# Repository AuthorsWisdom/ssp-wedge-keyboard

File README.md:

# Seven Swords Wedge Keyboard

This is an open-hardware 48-key (4 × 12 ortholinear) USB keyboard with an EC11 rotary encoder, built on an RP2040. It's designed for the Seven Swords Wedge desk console by Seven Swords Productions.

| Path | What | Licence |
|---|---|---|
| `keyboard-pcb/` | KiCad 9 project: schematic, PCB, generator scripts, fab outputs, outline DXF | **CERN-OHL-P-2.0** (`keyboard-pcb/LICENSE`) |
| `firmware/` | RMK-based Rust firmware (`rmk-wedge/`) and prebuilt UF2 | **MIT** (`firmware/rmk-wedge/LICENSE`) |

See `keyboard-pcb/README.md` for the build and fab instructions, and `keyboard-pcb/NOTICE.md` for attributions. The RP2040 core follows the Raspberry Pi "Minimal RP2040" reference design (MIT). Raspberry Pi is a trademark of Raspberry Pi Ltd. This is not a Raspberry Pi product.

USB IDs: the firmware currently uses RMK's test VID/PID. A pid.codes ID (1209:5357) is planned and not yet assigned.

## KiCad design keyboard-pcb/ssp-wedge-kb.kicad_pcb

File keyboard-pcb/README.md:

# Seven Swords Wedge — keyboard PCB (KB-P1)

An original 2-layer, 240 × 102 mm, 1.6 mm board: RP2040 + W25Q128 flash, USB-C (USB 2.0 device, 5.1 kΩ CC pull-downs, USBLC6-2 ESD), AMS1117-3.3, 48 MX hot-swap keys (4 × 12, COL2ROW, 1N4148W per key), and an EC11E15244G1 encoder with push. The RP2040 core follows the Raspberry Pi "Minimal RP2040" reference design (MIT, see NOTICE.md). Nothing here comes from Micro Journal.

**Status: design only.** Nothing has been ordered, fabbed, or uploaded, and nothing is tested on hardware.

## Pin map (matches firmware/rmk-wedge/keyboard.toml)
| Signal | GPIO |
|---|---|
| COL0–COL11 | GPIO0–GPIO11 |
| ROW0–ROW3 | GPIO12–GPIO15 |
| ROW4 (encoder push only, key (4,11) via D49) | GPIO18 |
| ENC_A / ENC_B | GPIO16 / GPIO17 |
| Free | GPIO19–GPIO29 (unconnected pads) |

SW49 is BOOTSEL and SW50 is RUN/reset. In the Wedge case they're reached with a SIM-eject pin through the two Ø3 poke holes in the case plate, over PCB (86, 94) = BOOT and (86, 85) = RESET. To flash: hold BOOT, tap RESET, release BOOT, and the `RPI-RP2` drive mounts over the internal cable. You don't need to open the case.

**J2 (3-pin SWD: SWCLK / SWDIO / GND) is DNP. Do not fit it.** A fitted header collides with the case plate (Wedge case v1.1). It's marked DNP on the board and in the schematic, it's left out of `bom-jlc.csv` and `cpl-jlc.csv`, and it's listed in `fab/dnp.csv` and `fab/hand-solder.csv` as DO NOT FIT. If SWD is ever needed, use pogo pins on the bare pads with the board out of the case.

## Files
| Path | What |
|---|---|
| `ssp-wedge-kb.kicad_sch` / `.kicad_pcb` / `.kicad_pro` / `.kicad_dru` | KiCad 9 project |
| `ssp-wedge-kb.net`, `reports/schematic.pdf` | netlist and schematic PDF |
| `reports/erc.rpt`, `reports/drc.rpt` | ERC: 0. DRC: 0 errors, 0 unconnected (notes below) |
| `route/ssp-wedge-kb.dsn` / `.ses` | Freerouting 2.5.0 input and result |
| `fab/ssp-wedge-kb-gerbers.zip` | Gerbers + Excellon drill (PTH/NPTH) + maps + job file |
| `fab/bom-jlc.csv`, `fab/cpl-jlc.csv` | JLCPCB BOM (LCSC #) and CPL: 82 top-side SMD parts |
| `fab/hand-solder.csv` | 48 bottom hot-swap sockets + the EC11 (not in the JLC BOM/CPL), plus a J2 row marked DNP |
| `fab/dnp.csv` | Do-not-fit parts (J2) and why |
| `renders/ssp-wedge-kb-top.png`, `-bottom.png` | 3D renders |
| `mech/ssp-wedge-kb-outline.dxf`, `mech/dims-note.md` | outline, holes, key grid, and keep-outs for the case |
| `LICENSE` | CERN-OHL-P v2 full text (the licence for this hardware) |
| `NOTICE.md` | licence summary and attributions |

## Licence
SPDX-License-Identifier: **CERN-OHL-P-2.0**. Copyright (c) 2026 Seven Swords Productions.

This hardware design is released under the CERN Open Hardware Licence Version 2, Permissive (full text in `LICENSE`). It covers the KiCad sources, the `gen/` scripts, the routing, and the fab outputs in this folder. The licence ID is also on the board's front silkscreen and on the schematic and PCB title blocks. The RP2040 core circuit credits Raspberry Pi's MIT-licensed Minimal RP2040 reference design (see `NOTICE.md`). The firmware (`../firmware`) is MIT, and so is the bot app.

You may use, modify, make and sell this design. Keep the licence notice and the NOTICE attributions. The design comes with no warranty (see CERN-OHL-P §6).

## Regenerate
The whole board is generated by scripts. Don't hand-edit the board, because the next run overwrites it.
```
cd gen
python3 gen_sch.py          # schematic from design.py (+ ERC / netlist)
python3 check_netlist.py    # schematic vs design.py: expect "mismatches: 0"
python3 gen_pcb.py          # placement, outline, holes, netclasses
python3 route.py dsn        # export Specctra DSN
python3 route.py route      # run Freerouting (about 10 to 20 min)
python3 route.py ses        # import the SES, clamp sub-0.15 mm stubs to 0.15, refill zones
cd .. && kicad-cli pcb drc --schematic-parity -o reports/drc.rpt ssp-wedge-kb.kicad_pcb
cd gen && python3 fab.py    # gerbers, drill, BOM/CPL, hand-solder list, renders, DXF
```
Requirements: KiCad 9.0.x (kicad-cli + pcbnew Python) and Freerouting 2.5.0. If you only change placement or the schematic, re-run gen_pcb and then `route.py ses` with the existing .ses to get the same routing back.

## Routing and DRC
- Freerouting reached **0 unrouted, 0 violations**: 1,026 track segments and 127 vias. There's a GND pour on both layers.
- Netclasses:
  - Power (VBUS/GND): 0.25 mm track, 0.6 mm via
  - Rail (+3V3/+1V1): 0.2 mm track, 0.6 mm via
  - Default: 0.2 mm track, 0.5/0.3 mm via
  - Clearance is 0.15 mm for all classes. Everything is within JLC's standard 2-layer capability (0.127 mm track and space, 0.3 mm drill).
- DRC with schematic parity: **0 errors, 0 unconnected.** The remaining warnings are expected:
  - 2 × silk_edge_clearance: the USB-C connector's own silk runs past the board edge where the mouth overhangs. JLC clips it.
  - 15 × net_conflict (parity warnings):
    - 2 for the EC11 mounting lugs, which are tied to GND on the PCB and have no schematic pin
    - 13 for no-connect pins (J1 SBU1/SBU2 and the unused RP2040 GPIO19–29), which have no copper
- `ssp-wedge-kb.kicad_dru` accepts one thermal spoke on the GND pads of two 0402 decoupling caps (C4, C6). They're boxed in by QFN fan-out tracks.

## Before any fab order (all open)
- **USB IDs.** The firmware still uses RMK's test VID/PID. We plan to apply for pid.codes **1209:5357**, which isn't assigned yet. Switch `keyboard.toml` only after the PR is merged.
- **Hardware testing.** Do a hardware bring-up first: check 3V3 rail current, BOOTSEL enumeration, and that flash boots.

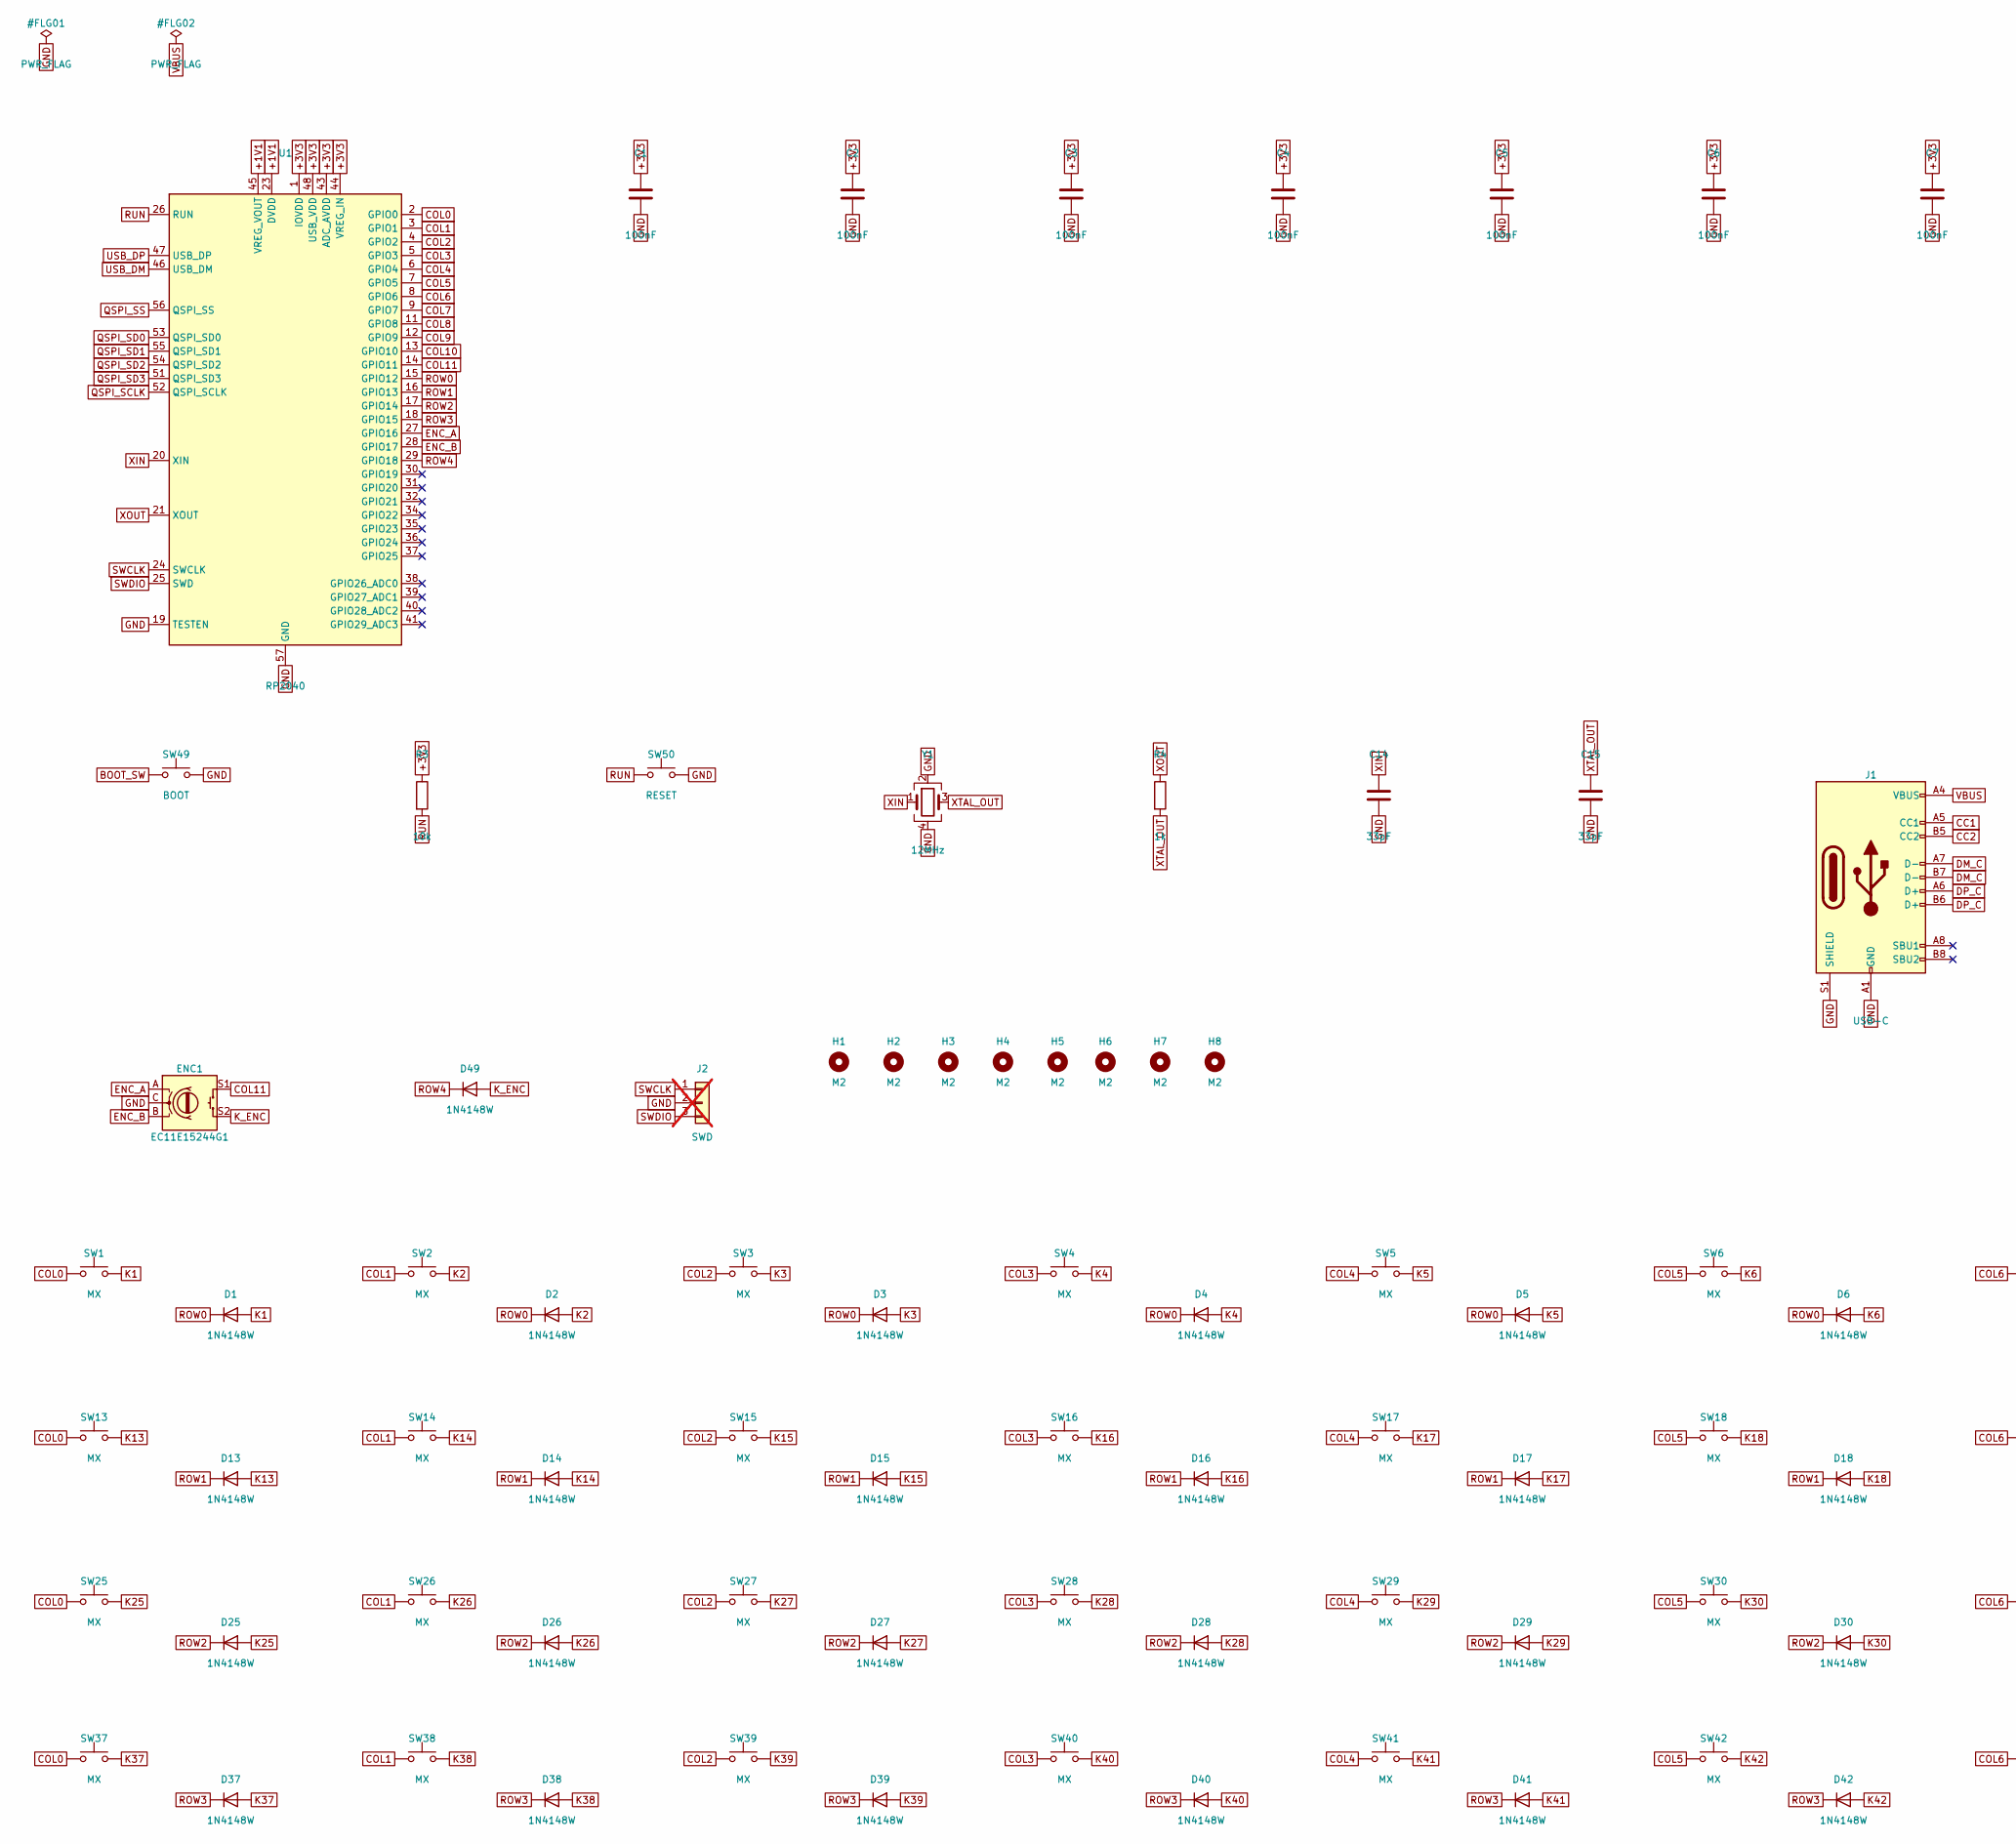
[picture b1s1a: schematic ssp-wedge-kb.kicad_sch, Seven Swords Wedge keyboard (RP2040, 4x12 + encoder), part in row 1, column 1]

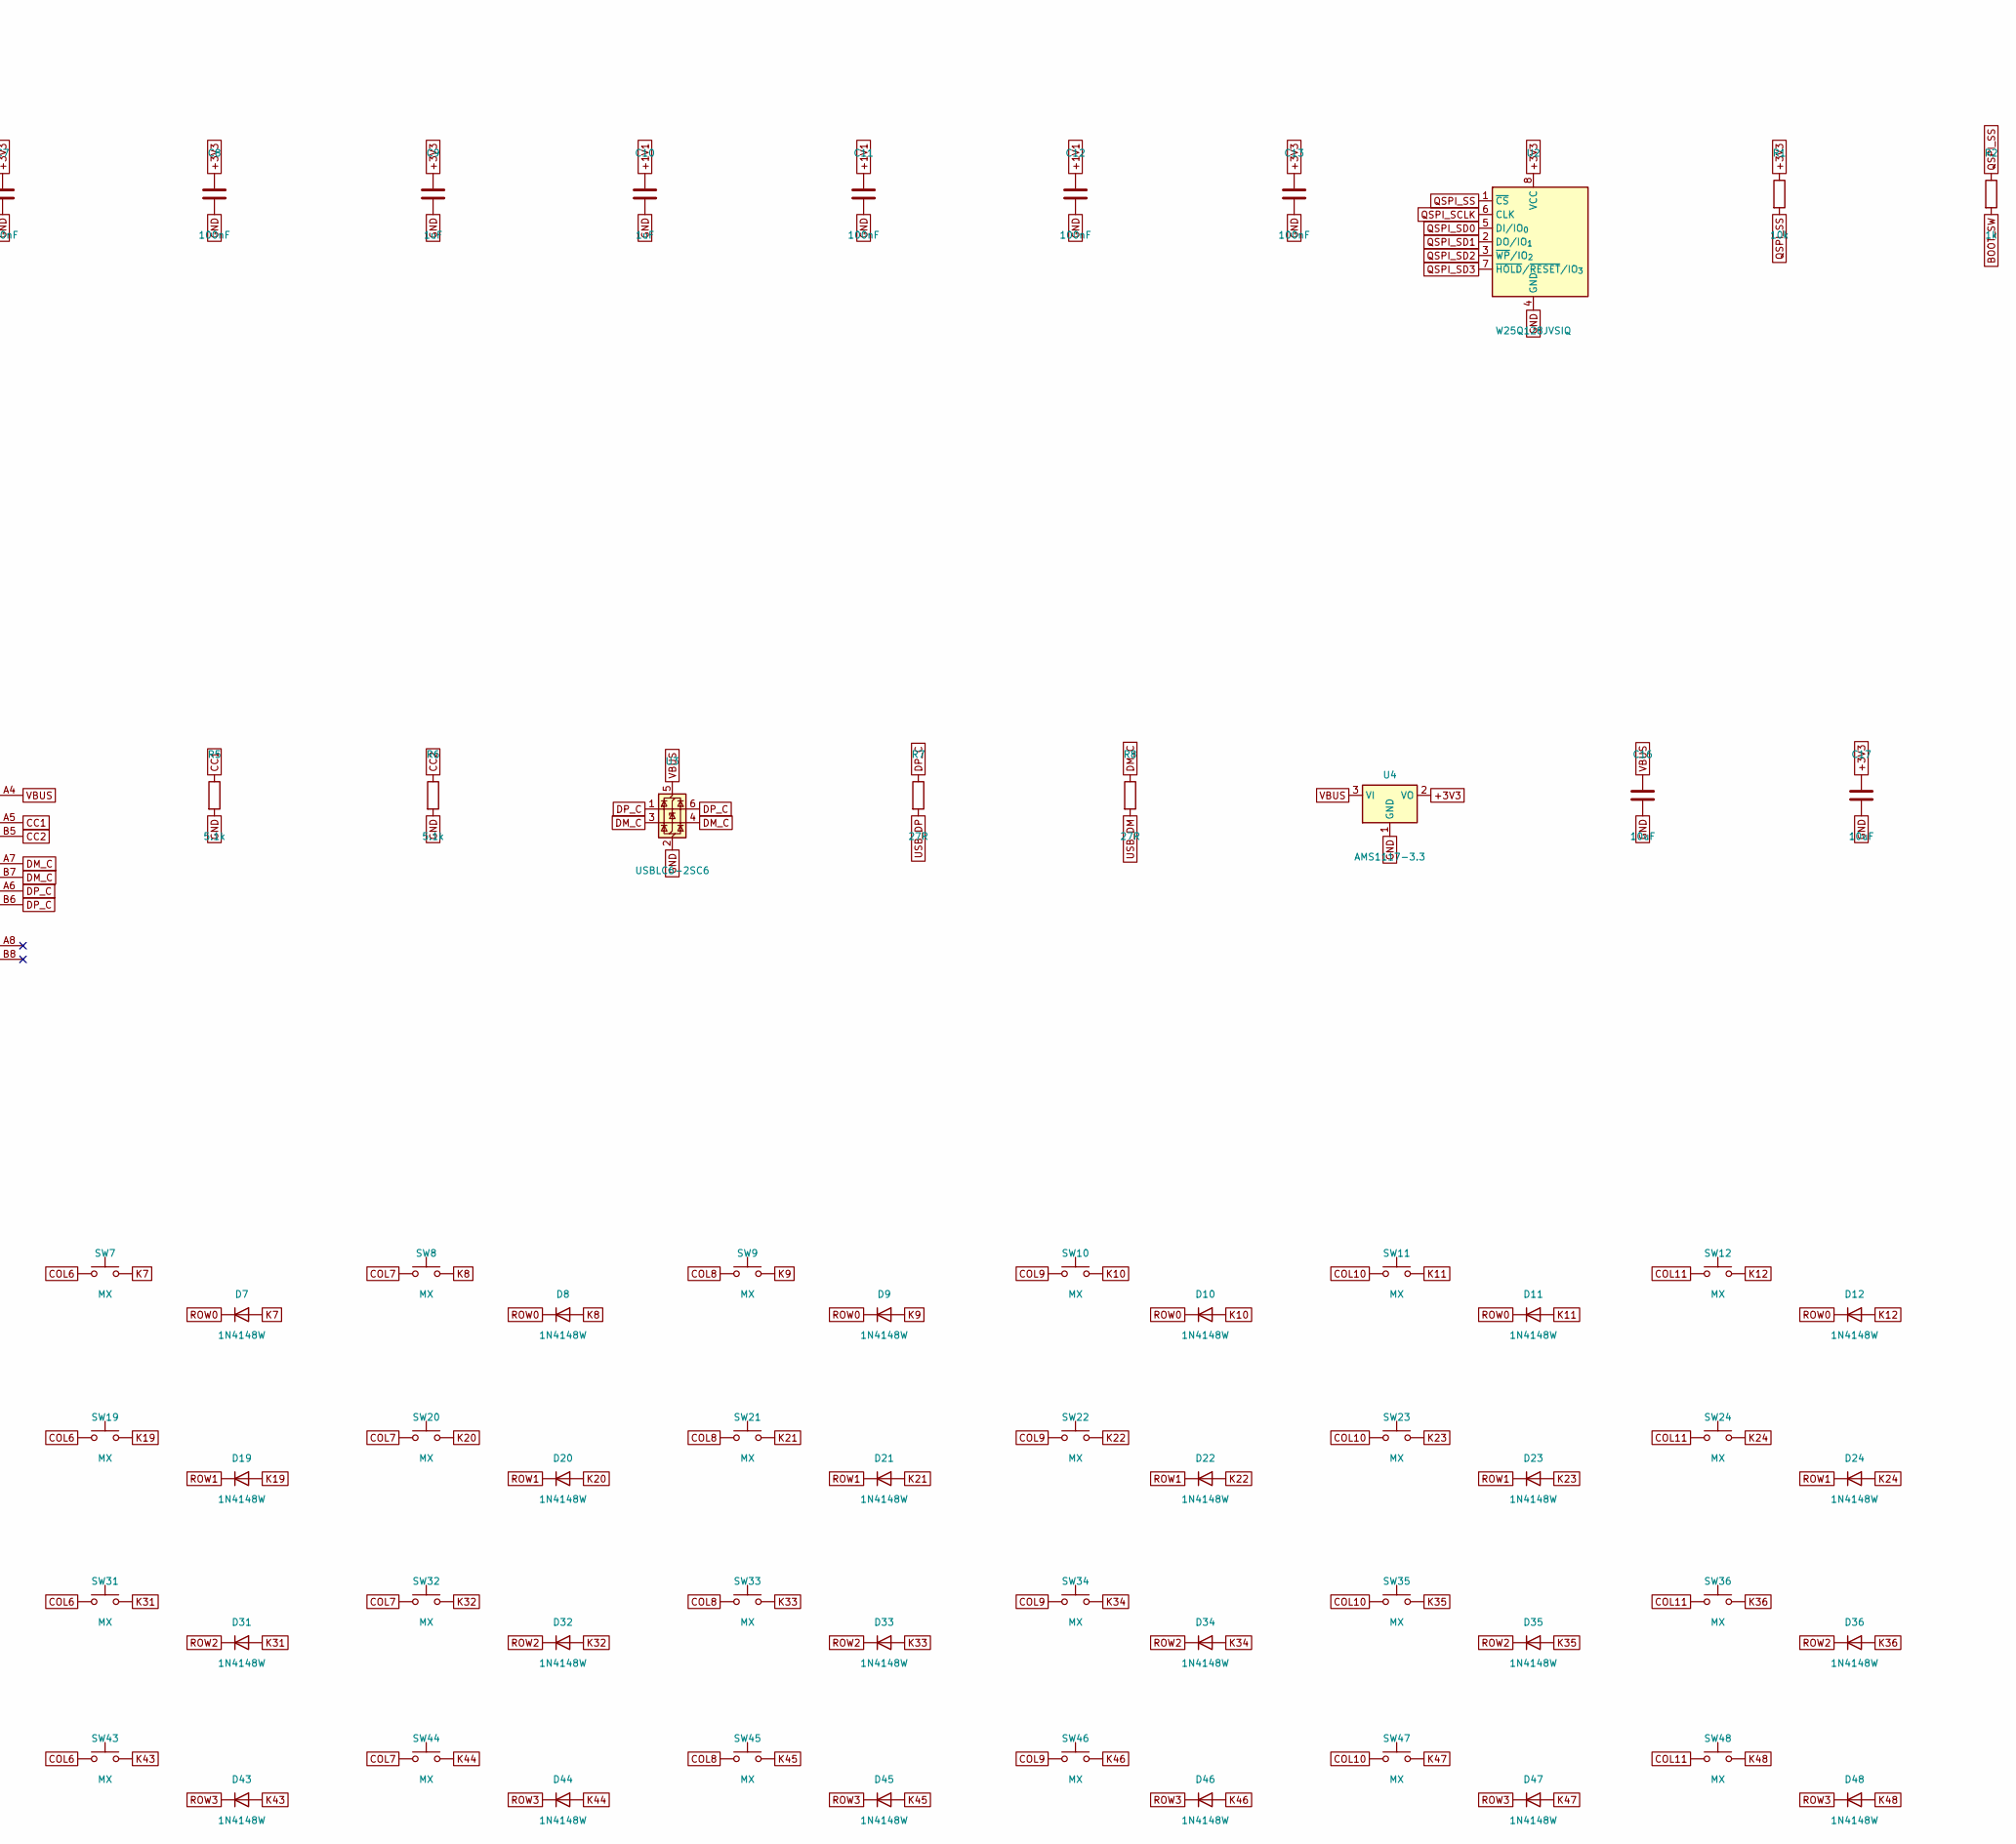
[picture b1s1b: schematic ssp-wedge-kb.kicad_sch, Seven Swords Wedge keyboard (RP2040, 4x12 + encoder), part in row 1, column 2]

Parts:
C1, C2, C3, C4, C5, C6, C7, C8, C11, C12, C13: 100nF; C_0402_1005Metric; LCSC C1525
C9, C10: 1uF; C_0402_1005Metric; LCSC C52923
C14, C15: 33pF; C_0402_1005Metric; LCSC C1562
C16, C17: 10uF; C_0805_2012Metric; LCSC C15850
D1, D2, D3, D4, D5, D6, D7, D8, D9, D10, D11, D12, D13, D14, D15, D16, D17, D18, D19, D20, D21, D22, D23, D24, D25, D26, D27, D28, D29, D30, D31, D32, D33, D34, D35, D36, D37, D38, D39, D40, D41, D42, D43, D44, D45, D46, D47, D48, D49: 1N4148W; D_SOD-123; LCSC C81598
ENC1: EC11E15244G1; RotaryEncoder_Alps_EC11E-Switch_Vertical_H20mm; LCSC C370970
H1, H2, H3, H4, H5, H6, H7, H8: M2; MountingHole_2.2mm_M2
J1: USB-C; USB_C_Receptacle_HRO_TYPE-C-31-M-12; LCSC C165948
J2: SWD; PinHeader_1x03_P2.54mm_Vertical; not fitted
R1, R3: 10k; R_0402_1005Metric; LCSC C25744
R2, R4: 1k; R_0402_1005Metric; LCSC C11702
R5, R6: 5.1k; R_0402_1005Metric; LCSC C25905
R7, R8: 27R; R_0402_1005Metric; LCSC C25100
SW1, SW2, SW3, SW4, SW5, SW6, SW7, SW8, SW9, SW10, SW11, SW12, SW13, SW14, SW15, SW16, SW17, SW18, SW19, SW20, SW21, SW22, SW23, SW24, SW25, SW26, SW27, SW28, SW29, SW30, SW31, SW32, SW33, SW34, SW35, SW36, SW37, SW38, SW39, SW40, SW41, SW42, SW43, SW44, SW45, SW46, SW47, SW48: MX; SW_MX_Hotswap_Kailh_1.00u; LCSC C5156480
SW49: BOOT; SW_Push_1P1T_XKB_TS-1187A; LCSC C318884
SW50: RESET; SW_Push_1P1T_XKB_TS-1187A; LCSC C318884
U1: RP2040; QFN-56-1EP_7x7mm_P0.4mm_EP3.2x3.2mm; LCSC C2040
U2: W25Q128JVSIQ; SOIC-8_5.3x5.3mm_P1.27mm; LCSC C97521
U3: USBLC6-2SC6; SOT-23-6; LCSC C7519
U4: AMS1117-3.3; SOT-223-3_TabPin2; LCSC C6186
Y1: 12MHz; Crystal_SMD_3225-4Pin_3.2x2.5mm; LCSC C9002

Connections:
+1V1: C10.1, C11.1, C12.1, U1.23 (DVDD), U1.45 (VREG_VOUT), U1.50 (DVDD)
+3V3: C1.1, C2.1, C3.1, C4.1, C5.1, C6.1, C7.1, C8.1, C9.1, C13.1, C17.1, R1.1, R3.1, U1.1 (IOVDD), U1.10 (IOVDD), U1.22 (IOVDD), U1.33 (IOVDD), U1.42 (IOVDD), U1.43 (ADC_AVDD), U1.44 (VREG_IN), U1.48 (USB_VDD), U1.49 (IOVDD), U2.8 (VCC), U4.2 (VO)
BOOT_SW: R2.2, SW49.1
CC1: J1.A5 (CC1), R5.1
CC2: J1.B5 (CC2), R6.1
COL0: SW1.1, SW13.1, SW25.1, SW37.1, U1.2 (GPIO0)
COL1: SW2.1, SW14.1, SW26.1, SW38.1, U1.3 (GPIO1)
COL2: SW3.1, SW15.1, SW27.1, SW39.1, U1.4 (GPIO2)
COL3: SW4.1, SW16.1, SW28.1, SW40.1, U1.5 (GPIO3)
COL4: SW5.1, SW17.1, SW29.1, SW41.1, U1.6 (GPIO4)
COL5: SW6.1, SW18.1, SW30.1, SW42.1, U1.7 (GPIO5)
COL6: SW7.1, SW19.1, SW31.1, SW43.1, U1.8 (GPIO6)
COL7: SW8.1, SW20.1, SW32.1, SW44.1, U1.9 (GPIO7)
COL8: SW9.1, SW21.1, SW33.1, SW45.1, U1.11 (GPIO8)
COL9: SW10.1, SW22.1, SW34.1, SW46.1, U1.12 (GPIO9)
COL10: SW11.1, SW23.1, SW35.1, SW47.1, U1.13 (GPIO10)
COL11: ENC1.S1, SW12.1, SW24.1, SW36.1, SW48.1, U1.14 (GPIO11)
DM_C: J1.A7 (D-), J1.B7 (D-), R8.1, U3.3 (I/O2), U3.4 (I/O2)
DP_C: J1.A6 (D+), J1.B6 (D+), R7.1, U3.1 (I/O1), U3.6 (I/O1)
ENC_A: ENC1.A, U1.27 (GPIO16)
ENC_B: ENC1.B, U1.28 (GPIO17)
GND: C1.2, C2.2, C3.2, C4.2, C5.2, C6.2, C7.2, C8.2, C9.2, C10.2, C11.2, C12.2, C13.2, C14.2, C15.2, C16.2, C17.2, ENC1.C, ENC1.MP, J1.A1 (GND), J1.A12 (GND), J1.B1 (GND), J1.B12 (GND), J1.S1 (SHIELD), J2.2, R5.2, R6.2, SW49.2, SW50.2, U1.19 (TESTEN), U1.57 (GND), U2.4 (GND), U3.2 (GND), U4.1 (GND), Y1.2, Y1.4
K1: D1.2 (A), SW1.2
K2: D2.2 (A), SW2.2
K3: D3.2 (A), SW3.2
K4: D4.2 (A), SW4.2
K5: D5.2 (A), SW5.2
K6: D6.2 (A), SW6.2
K7: D7.2 (A), SW7.2
K8: D8.2 (A), SW8.2
K9: D9.2 (A), SW9.2
K10: D10.2 (A), SW10.2
K11: D11.2 (A), SW11.2
K12: D12.2 (A), SW12.2
K13: D13.2 (A), SW13.2
K14: D14.2 (A), SW14.2
K15: D15.2 (A), SW15.2
K16: D16.2 (A), SW16.2
K17: D17.2 (A), SW17.2
K18: D18.2 (A), SW18.2
K19: D19.2 (A), SW19.2
K20: D20.2 (A), SW20.2
K21: D21.2 (A), SW21.2
K22: D22.2 (A), SW22.2
K23: D23.2 (A), SW23.2
K24: D24.2 (A), SW24.2
K25: D25.2 (A), SW25.2
K26: D26.2 (A), SW26.2
K27: D27.2 (A), SW27.2
K28: D28.2 (A), SW28.2
K29: D29.2 (A), SW29.2
K30: D30.2 (A), SW30.2
K31: D31.2 (A), SW31.2
K32: D32.2 (A), SW32.2
K33: D33.2 (A), SW33.2
K34: D34.2 (A), SW34.2
K35: D35.2 (A), SW35.2
K36: D36.2 (A), SW36.2
K37: D37.2 (A), SW37.2
K38: D38.2 (A), SW38.2
K39: D39.2 (A), SW39.2
K40: D40.2 (A), SW40.2
K41: D41.2 (A), SW41.2
K42: D42.2 (A), SW42.2
K43: D43.2 (A), SW43.2
K44: D44.2 (A), SW44.2
K45: D45.2 (A), SW45.2
K46: D46.2 (A), SW46.2
K47: D47.2 (A), SW47.2
K48: D48.2 (A), SW48.2
K_ENC: D49.2 (A), ENC1.S2
QSPI_SCLK: U1.52 (QSPI_SCLK), U2.6 (CLK)
QSPI_SD0: U1.53 (QSPI_SD0), U2.5 (DI/IO_{0})
QSPI_SD1: U1.55 (QSPI_SD1), U2.2 (DO/IO_{1})
QSPI_SD2: U1.54 (QSPI_SD2), U2.3 (~WP/IO_{2})
QSPI_SD3: U1.51 (QSPI_SD3), U2.7 (~HOLD/~RESET/IO_{3})
QSPI_SS: R1.2, R2.1, U1.56 (QSPI_SS), U2.1 (~CS)
ROW0: D1.1 (K), D2.1 (K), D3.1 (K), D4.1 (K), D5.1 (K), D6.1 (K), D7.1 (K), D8.1 (K), D9.1 (K), D10.1 (K), D11.1 (K), D12.1 (K), U1.15 (GPIO12)
ROW1: D13.1 (K), D14.1 (K), D15.1 (K), D16.1 (K), D17.1 (K), D18.1 (K), D19.1 (K), D20.1 (K), D21.1 (K), D22.1 (K), D23.1 (K), D24.1 (K), U1.16 (GPIO13)
ROW2: D25.1 (K), D26.1 (K), D27.1 (K), D28.1 (K), D29.1 (K), D30.1 (K), D31.1 (K), D32.1 (K), D33.1 (K), D34.1 (K), D35.1 (K), D36.1 (K), U1.17 (GPIO14)
ROW3: D37.1 (K), D38.1 (K), D39.1 (K), D40.1 (K), D41.1 (K), D42.1 (K), D43.1 (K), D44.1 (K), D45.1 (K), D46.1 (K), D47.1 (K), D48.1 (K), U1.18 (GPIO15)
ROW4: D49.1 (K), U1.29 (GPIO18)
RUN: R3.2, SW50.1, U1.26 (RUN)
SWCLK: J2.1, U1.24 (SWCLK)
SWDIO: J2.3, U1.25 (SWD)
USB_DM: R8.2, U1.46 (USB_DM)
USB_DP: R7.2, U1.47 (USB_DP)
VBUS: C16.1, J1.A4 (VBUS), J1.A9 (VBUS), J1.B4 (VBUS), J1.B9 (VBUS), U3.5 (VBUS), U4.3 (VI)
XIN: C14.1, U1.20 (XIN), Y1.1
XOUT: R4.1, U1.21 (XOUT)
XTAL_OUT: C15.1, R4.2, Y1.3

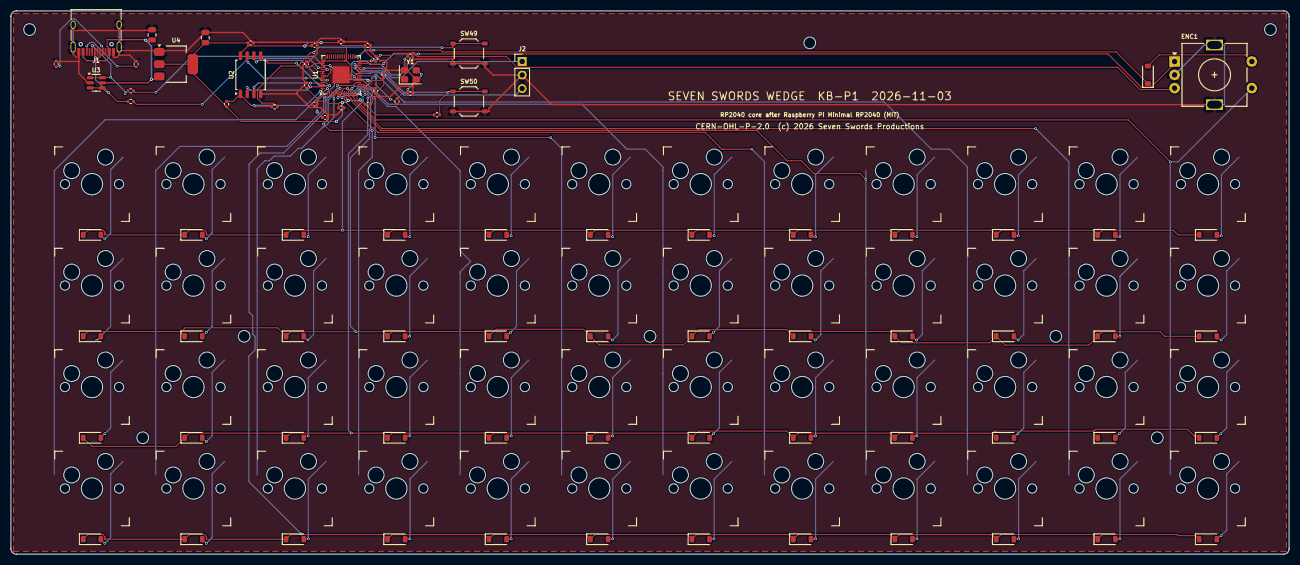
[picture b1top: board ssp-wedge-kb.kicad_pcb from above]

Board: 2 copper layers, 240.0 x 102.0 mm, 140 parts (0 on the bottom side), 91 nets.

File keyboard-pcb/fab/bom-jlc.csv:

Comment,Designator,Footprint,LCSC Part #
100nF,"C1,C2,C3,C4,C5,C6,C7,C8,C11,C12,C13",C_0402_1005Metric,C1525
1uF,"C9,C10",C_0402_1005Metric,C52923
33pF,"C14,C15",C_0402_1005Metric,C1562
10uF,"C16,C17",C_0805_2012Metric,C15850
1N4148W,"D1,D2,D3,D4,D5,D6,D7,D8,D9,D10,D11,D12,D13,D14,D15,D16,D17,D18,D19,D20,D21,D22,D23,D24,D25,D26,D27,D28,D29,D30,D31,D32,D33,D34,D35,D36,D37,D38,D39,D40,D41,D42,D43,D44,D45,D46,D47,D48,D49",D_SOD-123,C81598
USB-C,J1,USB_C_Receptacle_HRO_TYPE-C-31-M-12,C165948
10k,"R1,R3",R_0402_1005Metric,C25744
1k,"R2,R4",R_0402_1005Metric,C11702
5.1k,"R5,R6",R_0402_1005Metric,C25905
27R,"R7,R8",R_0402_1005Metric,C25100
BOOT,SW49,SW_Push_1P1T_XKB_TS-1187A,C318884
RESET,SW50,SW_Push_1P1T_XKB_TS-1187A,C318884
RP2040,U1,QFN-56-1EP_7x7mm_P0.4mm_EP3.2x3.2mm,C2040
W25Q128JVSIQ,U2,SOIC-8_5.3x5.3mm_P1.27mm,C97521
USBLC6-2SC6,U3,SOT-23-6,C7519
AMS1117-3.3,U4,SOT-223-3_TabPin2,C6186
12MHz,Y1,Crystal_SMD_3225-4Pin_3.2x2.5mm,C9002

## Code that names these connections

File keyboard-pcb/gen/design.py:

"""Seven Swords Wedge keyboard PCB: single source of truth for parts and nets.

Original SSP design. The RP2040 support circuit (flash, crystal, decoupling,
USB series resistors, BOOT/RUN) follows Raspberry Pi's MIT-licensed
"Minimal RP2040 board" reference design (Raspberry Pi Ltd).
See ../NOTICE.md.
"""
ROWS, COLS = 4, 12
PITCH = 19.05

# ---- GPIO map (keep in sync with firmware/keyboard.toml) ----
COL_GPIO = list(range(0, 12))       # COL0..COL11 -> GPIO0..GPIO11
ROW_GPIO = [12, 13, 14, 15]         # ROW0..ROW3  -> GPIO12..GPIO15
ENC_A_GPIO, ENC_B_GPIO = 16, 17
ENC_ROW_GPIO = 18                   # ROW4: encoder push sits in the matrix at (4, 11)

FP = {
    "R": "Resistor_SMD:R_0402_1005Metric",
    "C": "Capacitor_SMD:C_0402_1005Metric",
    "C10u": "Capacitor_SMD:C_0805_2012Metric",
    "D": "Diode_SMD:D_SOD-123",
    "MCU": "Package_DFN_QFN:QFN-56-1EP_7x7mm_P0.4mm_EP3.2x3.2mm",
    "FLASH": "Package_SO:SOIC-8_5.3x5.3mm_P1.27mm",
    "XTAL": "Crystal:Crystal_SMD_3225-4Pin_3.2x2.5mm",
    "USB": "Connector_USB:USB_C_Receptacle_HRO_TYPE-C-31-M-12",
    "ESD": "Package_TO_SOT_SMD:SOT-23-6",
    "LDO": "Package_TO_SOT_SMD:SOT-223-3_TabPin2",
    "ENC": "Rotary_Encoder:RotaryEncoder_Alps_EC11E-Switch_Vertical_H20mm",
    "BTN": "Button_Switch_SMD:SW_Push_1P1T_XKB_TS-1187A",
    "KEY": "SSP_Wedge:SW_MX_Hotswap_Kailh_1.00u",
    "HOLE": "MountingHole:MountingHole_2.2mm_M2",
    "SWD": "Connector_PinHeader_2.54mm:PinHeader_1x03_P2.54mm_Vertical",
}

# LCSC numbers are candidates; verify each one on lcsc.com before any order.
LCSC = {
    "RP2040": "C2040", "W25Q128JVSIQ": "C97521", "AMS1117-3.3": "C6186",
    "USBLC6-2SC6": "C7519", "TYPE-C-31-M-12": "C165948", "1N4148W": "C81598",
    "12MHz": "C9002", "100nF": "C1525", "1uF": "C52923", "10uF": "C15850",
    "33pF": "C1562", "27R": "C25100", "1k": "C11702", "10k": "C25744",
    "5.1k": "C25905", "TS-1187A": "C318884", "EC11": "C370970", "Kailh-MX-socket": "C5156480",
}

parts = []  # dicts: ref, lib, value, fp, lcsc, pins{pin:net}, side, dnp


def add(ref, lib, value, fp, pins, lcsc="", side="top", dnp=False, bom=True):
    parts.append(dict(ref=ref, lib=lib, value=value, fp=FP[fp], lcsc=lcsc, pins=pins,
                      side=side, dnp=dnp, bom=bom))


def R(ref, val, a, b):
    add(ref, "Device:R", val, "R", {"1": a, "2": b}, LCSC[val])


def C(ref, val, a, b="GND"):
    add(ref, "Device:C", val, "C10u" if val == "10uF" else "C", {"1": a, "2": b}, LCSC[val])


def build():
    parts.clear()
    # ---------------- MCU ----------------
    mcu = {"57": "GND", "26": "RUN", "47": "USB_DP", "46": "USB_DM",
           "56": "QSPI_SS", "53": "QSPI_SD0", "55": "QSPI_SD1", "54": "QSPI_SD2",
           "51": "QSPI_SD3", "52": "QSPI_SCLK", "20": "XIN", "21": "XOUT",
           "24": "SWCLK", "25": "SWDIO", "19": "GND",  # TESTEN -> GND
           "45": "+1V1", "23": "+1V1", "50": "+1V1",
           "48": "+3V3", "43": "+3V3", "44": "+3V3"}
    for p in ["1", "10", "22", "33", "42", "49"]:
        mcu[p] = "+3V3"
    gpio_pin = {0: "2", 1: "3", 2: "4", 3: "5", 4: "6", 5: "7", 6: "8", 7: "9",
                8: "11", 9: "12", 10: "13", 11: "14", 12: "15", 13: "16", 14: "17",
                15: "18", 16: "27", 17: "28", 18: "29", 19: "30", 20: "31", 21: "32",
                22: "34", 23: "35", 24: "36", 25: "37", 26: "38", 27: "39", 28: "40", 29: "41"}
    used = {}
    for c, g in enumerate(COL_GPIO):
        used[g] = f"COL{c}"
    for r, g in enumerate(ROW_GPIO):
        used[g] = f"ROW{r}"
    used[ENC_A_GPIO], used[ENC_B_GPIO], used[ENC_ROW_GPIO] = "ENC_A", "ENC_B", "ROW4"
    for g, pin in gpio_pin.items():
        mcu[pin] = used.get(g)  # None -> no-connect
    add("U1", "MCU_RaspberryPi:RP2040", "RP2040", "MCU", mcu, LCSC["RP2040"])

    # decoupling (per Raspberry Pi minimal design)
    for i in range(6):
        C(f"C{1+i}", "100nF", "+3V3")          # IOVDD x6
    C("C7", "100nF", "+3V3")                   # USB_VDD
    C("C8", "100nF", "+3V3")                   # ADC_AVDD
    C("C9", "1uF", "+3V3")                     # VREG_IN
    C("C10", "1uF", "+1V1")                    # VREG_VOUT
    C("C11", "100nF", "+1V1")                  # DVDD
    C("C12", "100nF", "+1V1")                  # DVDD
    C("C13", "100nF", "+3V3")                  # flash

    # ---------------- flash ----------------
    add("U2", "Memory_Flash:W25Q128JVS", "W25Q128JVSIQ", "FLASH",
        {"1": "QSPI_SS", "6": "QSPI_SCLK", "5": "QSPI_SD0", "2": "QSPI_SD1",
         "3": "QSPI_SD2", "7": "QSPI_SD3", "8": "+3V3", "4": "GND"}, LCSC["W25Q128JVSIQ"])
    R("R1", "10k", "+3V3", "QSPI_SS")          # CS pull-up
    R("R2", "1k", "QSPI_SS", "BOOT_SW")        # BOOT series R
    add("SW49", "Switch:SW_Push", "BOOT", "BTN", {"1": "BOOT_SW", "2": "GND"}, LCSC["TS-1187A"])

    # ---------------- RUN / reset ----------------
    R("R3", "10k", "+3V3", "RUN")
    add("SW50", "Switch:SW_Push", "RESET", "BTN", {"1": "RUN", "2": "GND"}, LCSC["TS-1187A"])

    # ---------------- crystal ----------------
    add("Y1", "Device:Crystal_GND24", "12MHz", "XTAL",
        {"1": "XIN", "3": "XTAL_OUT", "2": "GND", "4": "GND"}, LCSC["12MHz"])
    R("R4", "1k", "XOUT", "XTAL_OUT")
    C("C14", "33pF", "XIN")  # C9002 crystal is CL=20pF: 2*(20-~3.5pF stray) ~= 33pF
    C("C15", "33pF", "XTAL_OUT")

    # ---------------- USB-C + ESD + LDO ----------------
    add("J1", "Connector:USB_C_Receptacle_USB2.0_16P", "USB-C", "USB",
        {"S1": "GND", "A1": "GND", "A12": "GND", "B1": "GND", "B12": "GND",
         "A4": "VBUS", "A9": "VBUS", "B4": "VBUS", "B9": "VBUS",
         "A5": "CC1", "B5": "CC2", "A6": "DP_C", "B6": "DP_C", "A7": "DM_C", "B7": "DM_C",
         "A8": None, "B8": None}, LCSC["TYPE-C-31-M-12"])
    R("R5", "5.1k", "CC1", "GND")
    R("R6", "5.1k", "CC2", "GND")
    add("U3", "Power_Protection:USBLC6-2SC6", "USBLC6-2SC6", "ESD",
        {"1": "DP_C", "6": "DP_C", "3": "DM_C", "4": "DM_C", "5": "VBUS", "2": "GND"},
        LCSC["USBLC6-2SC6"])
    R("R7", "27R", "DP_C", "USB_DP")
    R("R8", "27R", "DM_C", "USB_DM")
    add("U4", "Regulator_Linear:AMS1117-3.3", "AMS1117-3.3", "LDO",
        {"3": "VBUS", "1": "GND", "2": "+3V3"}, LCSC["AMS1117-3.3"])
    C("C16", "10uF", "VBUS")
    C("C17", "10uF", "+3V3")

    # ---------------- encoder ----------------
    add("ENC1", "Device:RotaryEncoder_Switch", "EC11E15244G1", "ENC",
        {"A": "ENC_A", "B": "ENC_B", "C": "GND", "S1": "COL11", "S2": "K_ENC", "MP": "GND"},
        LCSC["EC11"], side="top")
    # push switch is matrix key (row 4, col 11), COL2ROW like the others
    add("D49", "Device:D", "1N4148W", "D", {"2": "K_ENC", "1": "ROW4"}, LCSC["1N4148W"])

    # ---------------- SWD header (not populated) ----------------
    add("J2", "Connector_Generic:Conn_01x03", "SWD", "SWD",
        {"1": "SWCLK", "2": "GND", "3": "SWDIO"}, dnp=True, bom=False)

    # ---------------- matrix (COL2ROW) ----------------
    n = 0
    for r in range(ROWS):
        for c in range(COLS):
            n += 1
            add(f"SW{n}", "Switch:SW_Push", "MX", "KEY",
                {"1": f"COL{c}", "2": f"K{n}"}, LCSC["Kailh-MX-socket"], side="bottom")
            add(f"D{n}", "Device:D", "1N4148W", "D",
                {"2": f"K{n}", "1": f"ROW{r}"}, LCSC["1N4148W"])

    # ---------------- mounting holes ----------------
    for i in range(1, 9):
        add(f"H{i}", "Mechanical:MountingHole", "M2", "HOLE", {}, bom=False)
    return parts


if __name__ == "__main__":
    build()
    nets = sorted({n for p in parts for n in p["pins"].values() if n})
    print(len(parts), "parts;", len(nets), "nets")

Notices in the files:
keyboard-pcb/ssp-wedge-kb.kicad_pcb:
CERN-OHL-P-2.0  (c) 2026 Seven Swords Productions
keyboard-pcb/ssp-wedge-kb.kicad_sch:
SPDX-License-Identifier: CERN-OHL-P-2.0  (c) 2026 Seven Swords Productions
